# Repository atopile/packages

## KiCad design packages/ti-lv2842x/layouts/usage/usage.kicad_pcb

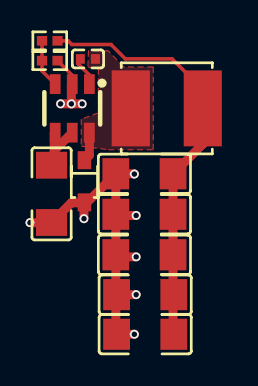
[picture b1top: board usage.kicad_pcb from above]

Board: 2 copper layers, 12 parts (0 on the bottom side), 7 nets.

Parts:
C1: 470nF ±10%; C0402
C2: 4.7µF ±10%; C1206
C3, C4, C5, C6, C7: 10µF ±10%; C1206
D1: SOD-323_L1.8-W1.3-LS2.5-RD
L1: L 22µH ±20%; IND-SMD_L5.0-W5.0_H4.0
R1: 102kΩ ±1%; R0402
R2: 30.9kΩ ±1%; R0402
U1: SOT-23-6_L2.9-W1.6-P0.95-LS2.8-BR

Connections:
anode: C3.2, C4.2, C5.2, C6.2, C7.2, D1.2, R2.2
cathode: C1.2, D1.1, L1.1, U1.6
hv: C2.1, U1.4, U1.5
lv: C2.2, U1.2
power-hv: C1.1, U1.1
power_out-hv: C3.1, C4.1, C5.1, C6.1, C7.1, L1.2, R1.1
ref_out-hv: R1.2, R2.1, U1.3

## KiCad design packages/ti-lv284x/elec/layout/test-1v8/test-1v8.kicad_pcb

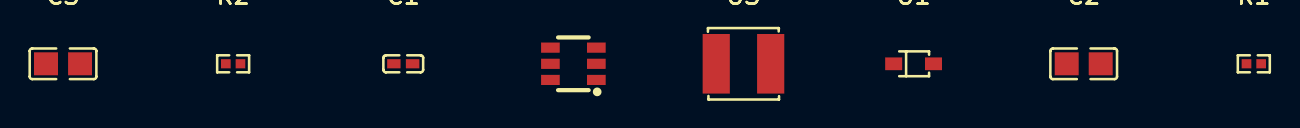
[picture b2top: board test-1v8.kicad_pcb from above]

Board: 2 copper layers, 8 parts (0 on the bottom side), 7 nets, no tracks yet.

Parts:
C1: 470nF ±20% 16V X5R; C0402-b3ef17
C2: 4.7µF ±10% 25V X5R; C0805-3b2e55
C3: 10µF ±10% 25V X5R; C0805-3b2e55
R1: 8.06kΩ ±1% 62.5mW; R0402-56259e
R2: 10kΩ ±1% 62.5mW; R0402-56259e
U1: SOD-323_L1.8-W1.3-LS2.5-RD
U2: SOT-23-6_L2.9-W1.6-P0.95-LS2.8-BR
U3: 10µH ±20%; IND-SMD_L4.0-W4.0

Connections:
CB: C1.1, U2.1
FB: R1.1, R2.2, U2.3
SW: C1.2, U1.1, U2.6, U3.1
gnd: C3.2, R1.2, U1.2
gnd-1: C2.2, U2.2
hv: C2.1, U2.4, U2.5
hv-1: C3.1, R2.1, U3.2

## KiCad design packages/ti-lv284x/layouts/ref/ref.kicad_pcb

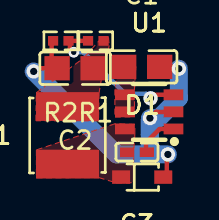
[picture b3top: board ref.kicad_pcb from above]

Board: 2 copper layers, 8 parts (0 on the bottom side), 6 nets.

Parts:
C1: 4.7µF ±10% 25V X5R; C0805
C2: 10µF ±10% 25V X5R; C0805
C3: 470nF ±20% 16V X5R; C0402
D1: SOD-323_L1.8-W1.3-LS2.5-RD
L1: IND-SMD_L4.0-W4.0
R1: 33kΩ ±1% 62.5mW; R0402
R2: 10kΩ ±1% 62.5mW; R0402
U1: SOT-23-6_L2.9-W1.6-P0.95-LS2.8-BR

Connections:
CB: C3.1, U1.1
FB: R1.2, R2.1, U1.3
K: C3.2, D1.1, L1.1, U1.6
VIN: C1.1, U1.4, U1.5
gnd: C1.2, C2.2, D1.2, R2.2, U1.2
hv: C2.1, L1.2, R1.1
